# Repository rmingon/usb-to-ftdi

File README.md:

# USB TO FTDI

Simple pcb with micro usb to header 2.54mm FTDI format

## PCB

## 3D

## Schematic

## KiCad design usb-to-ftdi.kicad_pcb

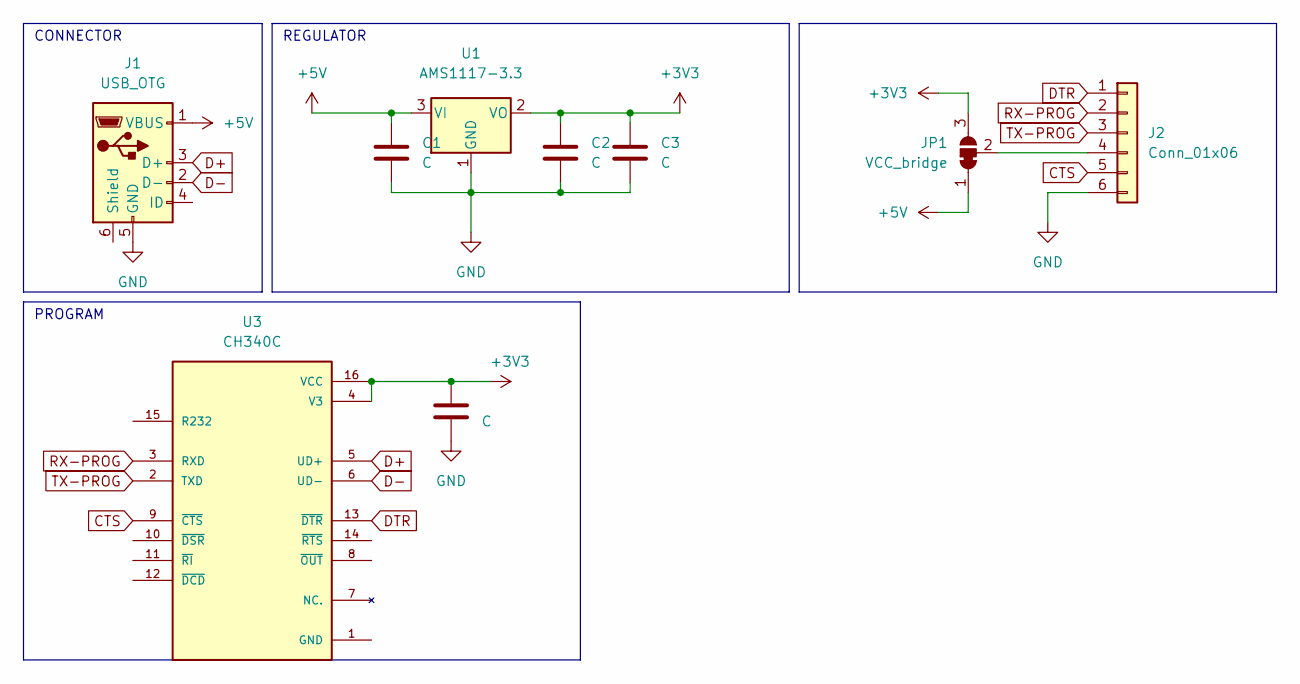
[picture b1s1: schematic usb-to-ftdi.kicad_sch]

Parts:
C1, C2, C3, C4: C; C_0603_1608Metric
J1: USB_OTG; USB_Micro-B_Amphenol_10118194_Horizontal
J2: Conn_01x06; PinHeader_1x06_P2.54mm_Vertical
JP1: VCC_bridge; SolderJumper-3_P1.3mm_Bridged12_Pad1.0x1.5mm
U1: AMS1117-3.3; SOT-223-3_TabPin2
U3: CH340C; SOIC127P600X180-16N; PARTREV 2G

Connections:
+3V3: C2.1, C3.1, C4.1, JP1.3 (B), U1.2 (VO), U3.4 (V3), U3.16 (VCC)
+5V: C1.1, J1.1 (VBUS), JP1.1 (A), U1.3 (VI)
CTS: J2.5, U3.9 (~CTS)
D+: J1.3 (D+), U3.5 (UD+)
D-: J1.2 (D-), U3.6 (UD-)
DTR: J2.1, U3.13 (~DTR)
GND: C1.2, C2.2, C3.2, C4.2, J1.5 (GND), J2.6, U1.1 (GND)
unnamed: J2.4, JP1.2 (C)
RX-PROG: J2.2, U3.3 (RXD)
TX-PROG: J2.3, U3.2 (TXD)

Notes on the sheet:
CONNECTOR
REGULATOR
PROGRAM

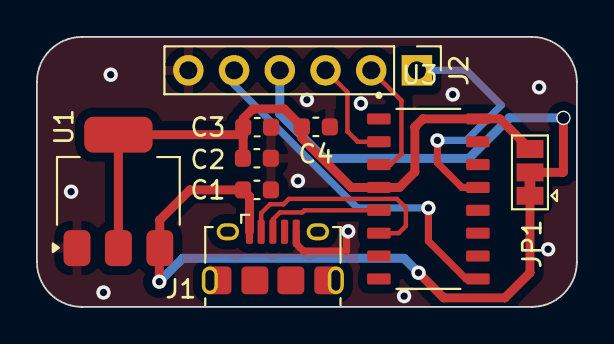
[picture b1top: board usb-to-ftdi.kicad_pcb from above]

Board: 2 copper layers, 30.0 x 15.0 mm, 9 parts (0 on the bottom side), 10 nets.

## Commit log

2025-01-16 update wiring + add jumper vcc
2025-01-16 add photos
2025-01-16 add pcb + wiring
2025-01-16 add readme
